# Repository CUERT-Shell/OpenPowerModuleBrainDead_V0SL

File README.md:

# OpenPowerModuleBrainDead_V0SL

Kicad Design 
You can view on https://kicanvas.org (for non kicad users)

## Power Module Board

Minimal BLDC drive hardware
Minimal Fabrication requirements , Single Layer PCB

### The hardware 
* 3phase H-bridge and all its related circuitry (MGD , Snubber , decoupling , etc)

Requires External 12V supply in addition to DC bus voltage

## Power Module Interface Board

* IDC-2x15 Connector to be interfaced with a controller/MCU
* 12V-->5V buck converter , 3.3V LDO
* Hall Sensor Conditioning Circuits
* Back Emf Zero cross detection circuitry
* Phase Voltage Conditioning Circuitry
* 3x NTC interface
* IDC-2x15 Connector to be interfaced with a controller/MCU
* LED as logic indicators

Requires External 12V supply

### Repo Structure
* PowerModule : Power Module Design Files
* PowerModuleInterface : Power Module Interface Design Files
* LIB : Project Components library
* Doc : Design Reference , guide , step file , etc...

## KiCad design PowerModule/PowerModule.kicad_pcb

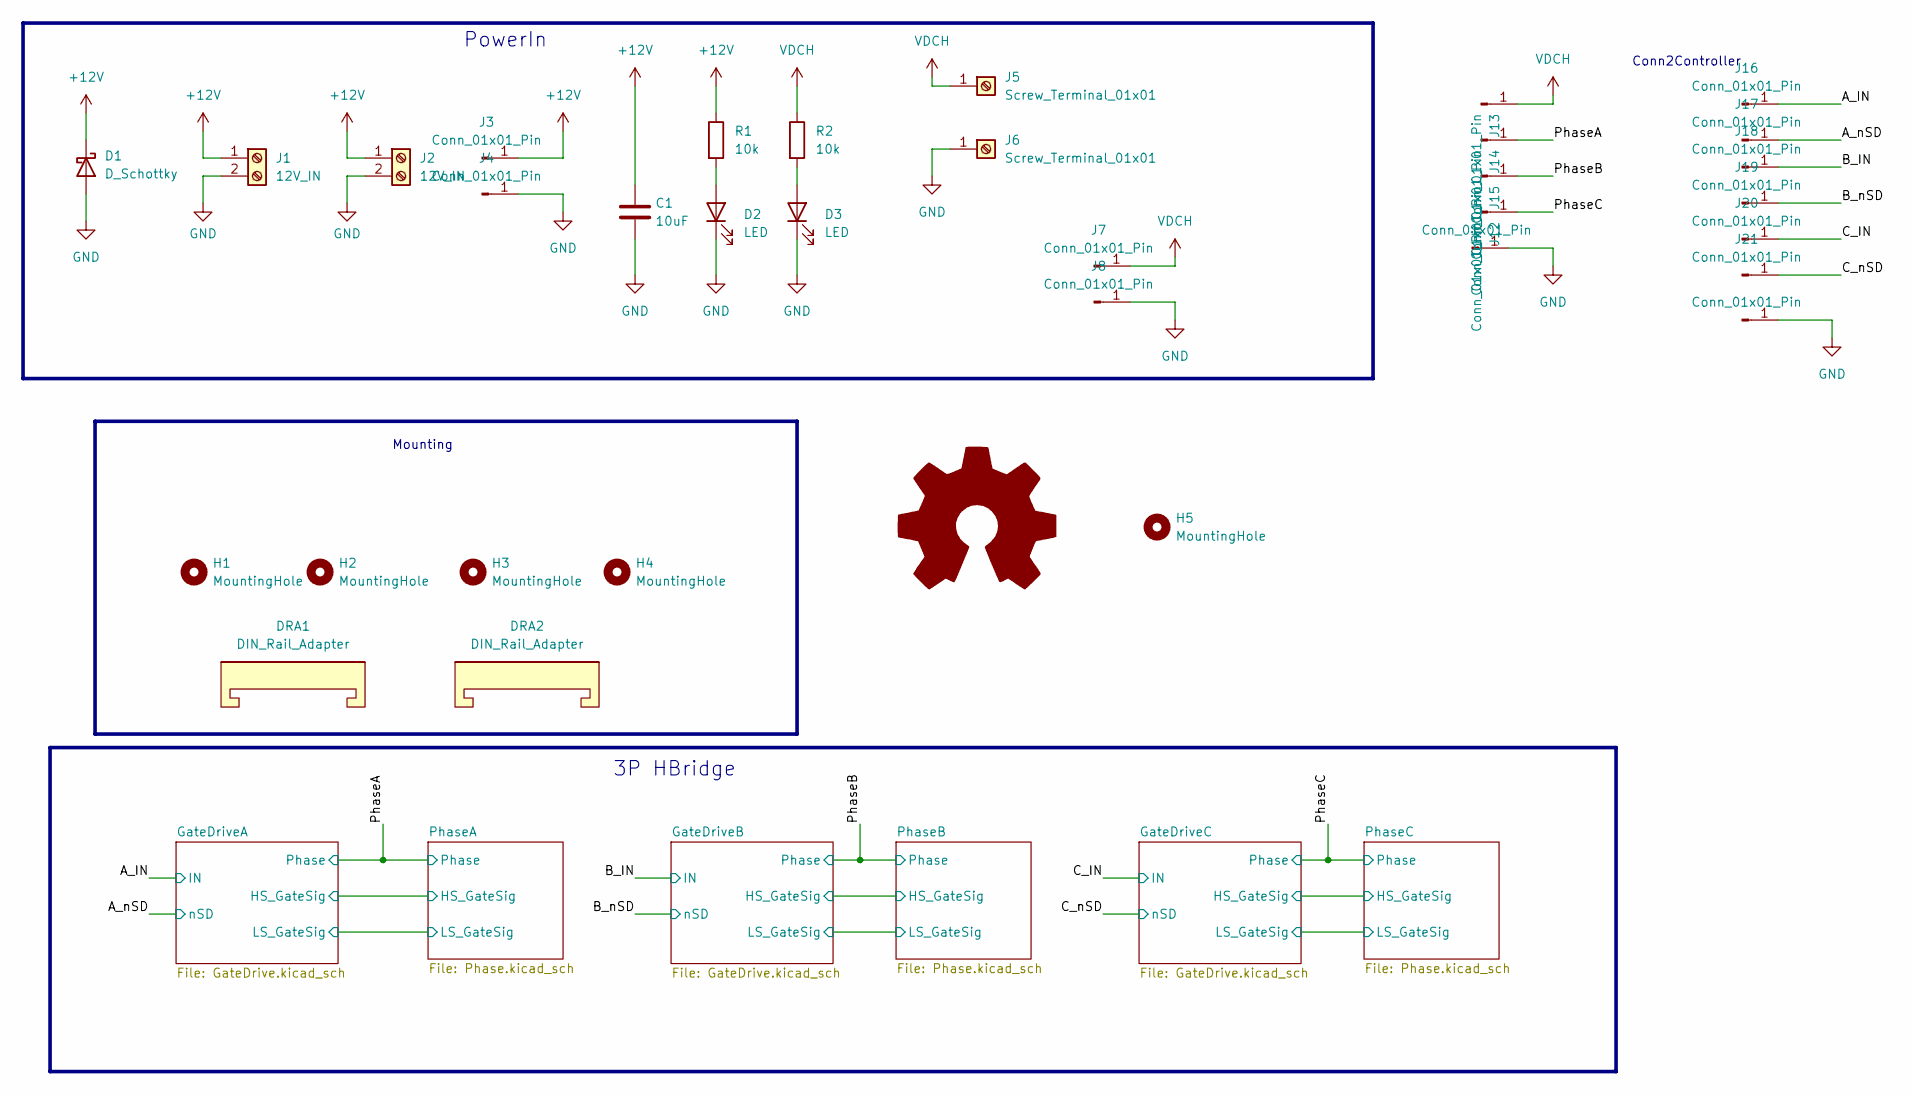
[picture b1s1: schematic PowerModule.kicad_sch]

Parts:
C1: 10uF; C_1206_3216Metric
D1: D_Schottky; D_SMC-RM10_Universal_Handsoldering
D2, D3: LED; LED_1206_3216Metric_Pad1.42x1.75mm_HandSolder
DRA1, DRA2: DIN_Rail_Adapter; DinRailPCBClip_P15
H1, H2, H3, H4: MountingHole; MountingHole_3.2mm_M3_DIN965
H5: MountingHole; KiCad-Logo2_12mm_SilkScreen
J1, J2: 12V_IN; TerminalBlock_Phoenix_PT-1,5-2-3.5-H_1x02_P3.50mm_Horizontal
J3, J4, J7, J8, J11, J12, J13, J14, J15, J16, J17, J18, J19, J20, J21, J22: Conn_01x01_Pin; WirePad_2.5x5
J5, J6: Screw_Terminal_01x01; D5mm_WirePad
R1, R2: 10k; R_1206_3216Metric_Pad1.30x1.75mm_HandSolder

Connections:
+12V: C1.1, D1.1 (K), J1.1, J2.1, J3.1, R1.1; also elsewhere on the board
/A_IN: J16.1; also elsewhere on the board
/A_nSD: J17.1; also elsewhere on the board
/B_IN: J18.1; also elsewhere on the board
/B_nSD: J19.1; also elsewhere on the board
/C_IN: J20.1; also elsewhere on the board
/C_nSD: J21.1; also elsewhere on the board
/PhaseA: J14.1; also elsewhere on the board
/PhaseB: J15.1; also elsewhere on the board
/PhaseC: J12.1; also elsewhere on the board
GND: C1.2, D1.2 (A), D2.1 (K), D3.1 (K), J1.2, J2.2, J4.1, J6.1, J8.1, J11.1, J22.1; also elsewhere on the board
unnamed: D2.2 (A), R1.2
unnamed: D3.2 (A), R2.2
VDCH: J5.1, J7.1, J13.1, R2.1; also elsewhere on the board

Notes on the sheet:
Mounting
3P HBridge
Conn2Controller
PowerIn

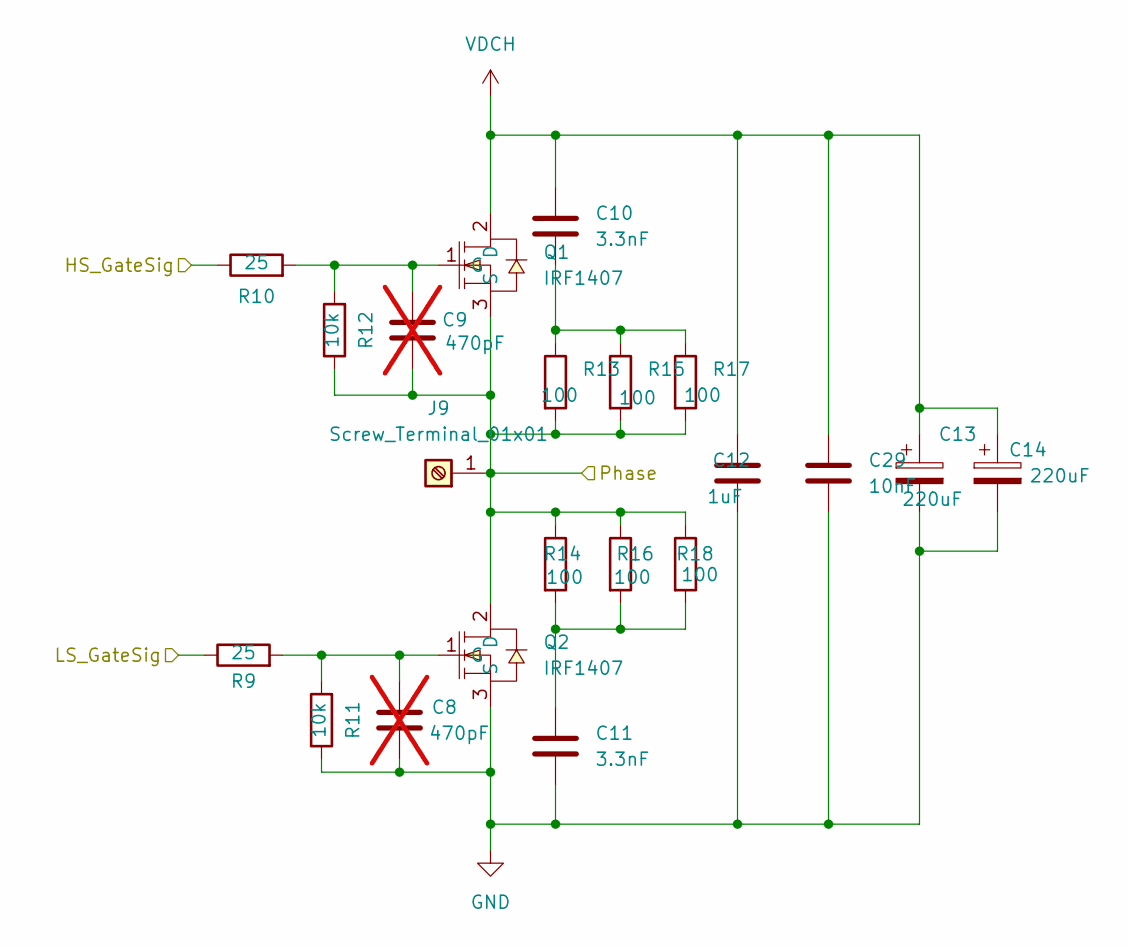
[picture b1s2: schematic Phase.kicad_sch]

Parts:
C8, C9: 470pF; C_1206_3216Metric; not fitted
C10, C11: 3.3nF; C_Rect_L7.2mm_W3.5mm_P5.00mm_FKS2_FKP2_MKS2_MKP2
C12: 1uF; C_Rect_L9.0mm_W5.1mm_P7.50mm_MKT
C13: 220uF; CP_Radial_Horizontal_P5.00_Up
C14: 220uF; CP_Radial_Horizontal_P5.00_Down
C29: 10nF; C_Rect_L7.2mm_W3.5mm_P5.00mm_FKS2_FKP2_MKS2_MKP2
J9: Screw_Terminal_01x01; D5mm_WirePad
Q1, Q2: IRF1407; TO-220-3_Horizontal_TabUp; LCSC Part C33129604
R9, R10: 25; R_1206_3216Metric
R11, R12: 10k; R_1206_3216Metric
R13, R14, R15, R16, R17, R18: 100; R_1206_3216Metric

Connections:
/GateDriveA/HS_GateSig: R10.1; also elsewhere on the board
/GateDriveA/LS_GateSig: R9.1; also elsewhere on the board
/PhaseA: C9.2, J9.1, Q1.3 (S), Q2.2 (D), R12.1, R13.2, R14.1, R15.2, R16.1, R17.2, R18.1; also elsewhere on the board
GND: C8.2, C11.2, C12.2, C13.2, C14.2, C29.2, Q2.3 (S), R11.1; also elsewhere on the board
unnamed: C10.2, R13.1, R15.1, R17.1
unnamed: C11.1, R14.2, R16.2, R18.2
unnamed: C9.1, Q1.1 (G), R10.2, R12.2
unnamed: C8.1, Q2.1 (G), R9.2, R11.2
VDCH: C10.1, C12.1, C13.1, C14.1, C29.1, Q1.2 (D); also elsewhere on the board

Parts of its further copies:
C15, C16, C22, C23: 470pF; C_1206_3216Metric; not fitted
C17, C18, C24, C25: 3.3nF; C_Rect_L7.2mm_W3.5mm_P5.00mm_FKS2_FKP2_MKS2_MKP2
C19, C26: 1uF; C_Rect_L9.0mm_W5.1mm_P7.50mm_MKT
C20, C27: 220uF; CP_Radial_Horizontal_P5.00_Up
C21, C28: 220uF; CP_Radial_Horizontal_P5.00_Down
C30, C31: 10nF; C_Rect_L7.2mm_W3.5mm_P5.00mm_FKS2_FKP2_MKS2_MKP2
J10, J23: Screw_Terminal_01x01; D5mm_WirePad
Q3, Q4, Q5, Q6: IRF1407; TO-220-3_Horizontal_TabUp; LCSC Part C33129604
R19, R20, R29, R30: 25; R_1206_3216Metric
R21, R22, R31, R32: 10k; R_1206_3216Metric
R23, R24, R25, R26, R27, R28, R33, R34, R35, R36, R37, R38: 100; R_1206_3216Metric

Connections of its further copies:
/GateDriveB/HS_GateSig: R20.1; also elsewhere on the board
/GateDriveB/LS_GateSig: R19.1; also elsewhere on the board
/GateDriveC/HS_GateSig: R30.1; also elsewhere on the board
/GateDriveC/LS_GateSig: R29.1; also elsewhere on the board
/PhaseB: C16.2, J10.1, Q3.3 (S), Q4.2 (D), R22.1, R23.2, R24.1, R25.2, R26.1, R27.2, R28.1; also elsewhere on the board
/PhaseC: C23.2, J23.1, Q5.3 (S), Q6.2 (D), R32.1, R33.2, R34.1, R35.2, R36.1, R37.2, R38.1; also elsewhere on the board
GND: C15.2, C18.2, C19.2, C20.2, C21.2, C22.2, C25.2, C26.2, C27.2, C28.2, C30.2, C31.2, Q4.3 (S), Q6.3 (S), R21.1, R31.1; also elsewhere on the board
unnamed: C17.2, R23.1, R25.1, R27.1
unnamed: C18.1, R24.2, R26.2, R28.2
unnamed: C24.2, R33.1, R35.1, R37.1
unnamed: C25.1, R34.2, R36.2, R38.2
unnamed: C16.1, Q3.1 (G), R20.2, R22.2
unnamed: C15.1, Q4.1 (G), R19.2, R21.2
unnamed: C23.1, Q5.1 (G), R30.2, R32.2
unnamed: C22.1, Q6.1 (G), R29.2, R31.2
VDCH: C17.1, C19.1, C20.1, C21.1, C24.1, C26.1, C27.1, C28.1, C30.1, C31.1, Q3.2 (D), Q5.2 (D); also elsewhere on the board

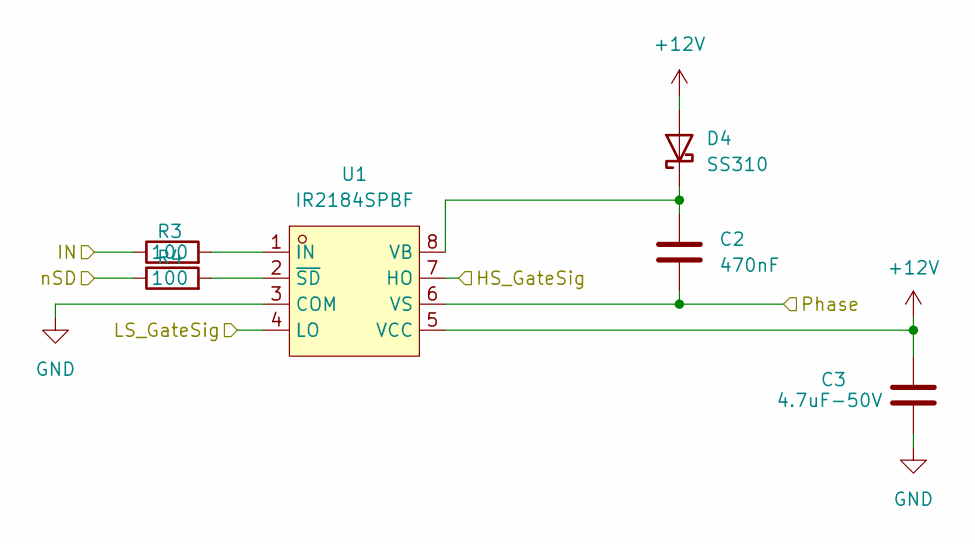
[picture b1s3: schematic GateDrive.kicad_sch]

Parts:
C2: 470nF; C_Rect_L9.0mm_W5.1mm_P7.50mm_MKT
C3: 4.7uF-50V; C_1206_3216Metric
D4: SS310; D_SMC-RM10_Universal_Handsoldering
R3, R4: 100; R_1206_3216Metric
U1: IR2184SPBF; SOIC-8_L5.0-W4.0-P1.27-LS6.0-BL; LCSC Part C537610

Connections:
+12V: C3.1, D4.2 (A), U1.5 (VCC); also elsewhere on the board
/A_IN: R3.1; also elsewhere on the board
/A_nSD: R4.1; also elsewhere on the board
/GateDriveA/HS_GateSig: U1.7 (HO); also elsewhere on the board
/GateDriveA/LS_GateSig: U1.4 (LO); also elsewhere on the board
/PhaseA: C2.2, U1.6 (VS); also elsewhere on the board
GND: C3.2, U1.3 (COM); also elsewhere on the board
unnamed: C2.1, D4.1 (K), U1.8 (VB)
unnamed: R3.2, U1.1 (IN)
unnamed: R4.2, U1.2 (~SD)

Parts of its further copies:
C4, C6: 470nF; C_Rect_L9.0mm_W5.1mm_P7.50mm_MKT
C5, C7: 4.7uF-50V; C_1206_3216Metric
D5, D6: SS310; D_SMC-RM10_Universal_Handsoldering
R5, R6, R7, R8: 100; R_1206_3216Metric
U2, U3: IR2184SPBF; SOIC-8_L5.0-W4.0-P1.27-LS6.0-BL; LCSC Part C537610

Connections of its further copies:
+12V: C5.1, C7.1, D5.2 (A), D6.2 (A), U2.5 (VCC), U3.5 (VCC); also elsewhere on the board
/B_IN: R5.1; also elsewhere on the board
/B_nSD: R6.1; also elsewhere on the board
/C_IN: R7.1; also elsewhere on the board
/C_nSD: R8.1; also elsewhere on the board
/GateDriveB/HS_GateSig: U2.7 (HO); also elsewhere on the board
/GateDriveB/LS_GateSig: U2.4 (LO); also elsewhere on the board
/GateDriveC/HS_GateSig: U3.7 (HO); also elsewhere on the board
/GateDriveC/LS_GateSig: U3.4 (LO); also elsewhere on the board
/PhaseB: C4.2, U2.6 (VS); also elsewhere on the board
/PhaseC: C6.2, U3.6 (VS); also elsewhere on the board
GND: C5.2, C7.2, U2.3 (COM), U3.3 (COM); also elsewhere on the board
unnamed: C4.1, D5.1 (K), U2.8 (VB)
unnamed: C6.1, D6.1 (K), U3.8 (VB)
unnamed: R5.2, U2.1 (IN)
unnamed: R6.2, U2.2 (~SD)
unnamed: R7.2, U3.1 (IN)
unnamed: R8.2, U3.2 (~SD)

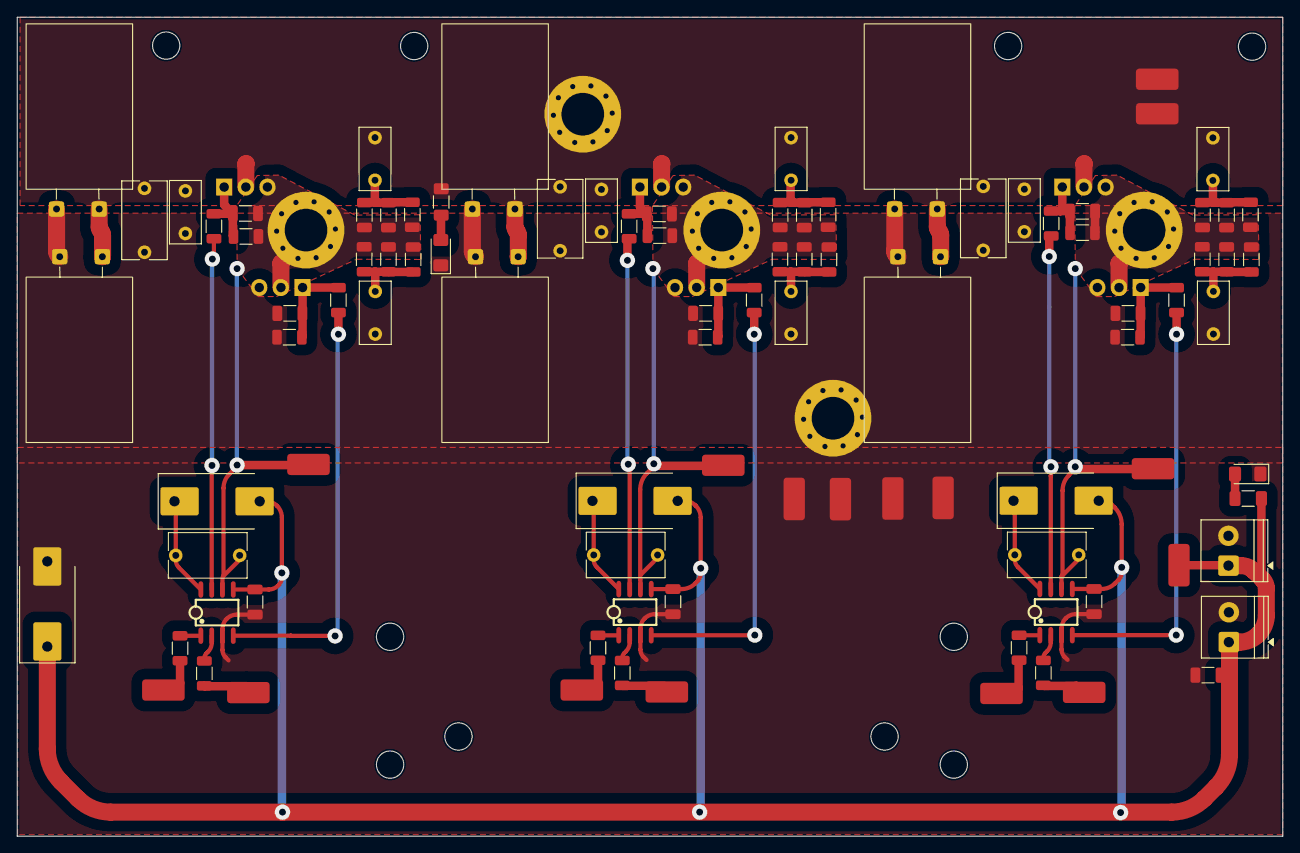
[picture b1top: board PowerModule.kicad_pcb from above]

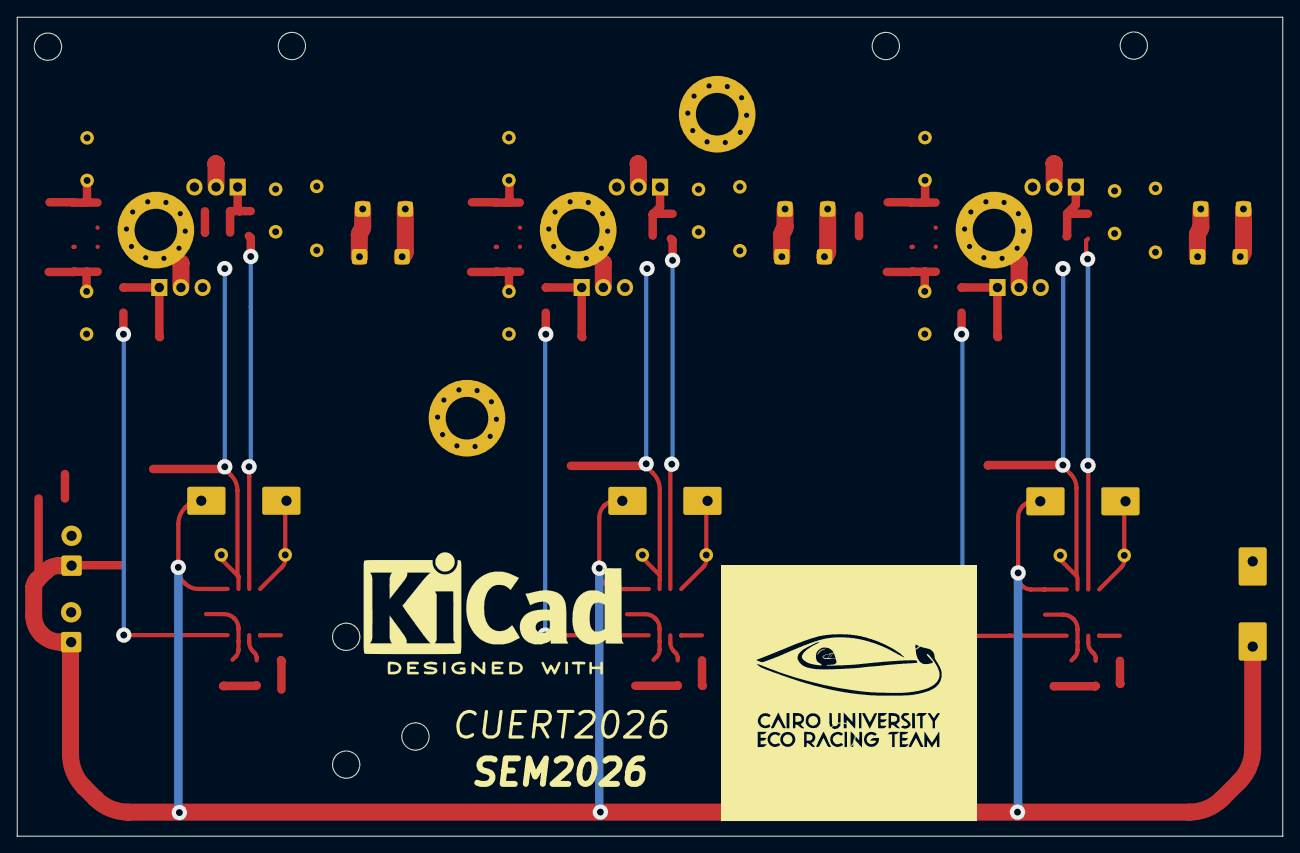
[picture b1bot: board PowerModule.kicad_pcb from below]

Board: 2 copper layers, 148.5 x 96.1 mm, 114 parts (7 on the bottom side), 41 nets.

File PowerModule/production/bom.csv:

Designator,Footprint,Quantity,Value,LCSC Part #
C1,1206,1,10uF,
"C10, C11, C17, C18, C24, C25",C_Rect_L7.2mm_W3.5mm_P5.00mm_FKS2_FKP2_MKS2_MKP2,6,3.3nF,
"C12, C19, C26",C_Rect_L9.0mm_W5.1mm_P7.50mm_MKT,3,1uF,
"C13, C20, C27",CP_Radial_Horizontal_P5.00_Up,3,220uF,
"C14, C21, C28",CP_Radial_Horizontal_P5.00_Down,3,220uF,
"C15, C16, C22, C23, C8, C9",1206,6,470pF,
"C2, C4, C6",C_Rect_L9.0mm_W5.1mm_P7.50mm_MKT,3,470nF,
"C29, C30, C31",C_Rect_L7.2mm_W3.5mm_P5.00mm_FKS2_FKP2_MKS2_MKP2,3,10nF,
"C3, C5, C7",1206,3,4.7uF-50V,
D1,D_SMC-RM10_Universal_Handsoldering,1,D_Schottky,
"D2, D3",1206,2,LED,
"D4, D5, D6",D_SMC-RM10_Universal_Handsoldering,3,SS310,
"DRA1, DRA2",DinRailPCBClip_P15,2,DIN_Rail_Adapter,
"J1, J2","TerminalBlock_Phoenix_PT-1,5-2-3.5-H_1x02_P3.50mm_Horizontal",2,12V_IN,
"J10, J23, J5, J6, J9",D5mm_WirePad,5,Screw_Terminal_01x01,
"J11, J12, J13, J14, J15, J16, J17, J18, J19, J20, J21, J22, J3, J4, J7, J8",WirePad_2.5x5,16,Conn_01x01_Pin,
"Q1, Q2, Q3, Q4, Q5, Q6",TO-220-3_Horizontal_TabUp,6,IRF1407,C33129604
"R1, R11, R12, R2, R21, R22, R31, R32",1206,8,10k,
"R10, R19, R20, R29, R30, R9",1206,6,25,
"R13, R14, R15, R16, R17, R18, R23, R24, R25, R26, R27, R28, R3, R33, R34, R35, R36, R37, R38, R4, R5, R6, R7, R8",1206,24,100,
"U1, U2, U3",SOIC-8_L5.0-W4.0-P1.27-LS6.0-BL,3,IR2184SPBF,C537610

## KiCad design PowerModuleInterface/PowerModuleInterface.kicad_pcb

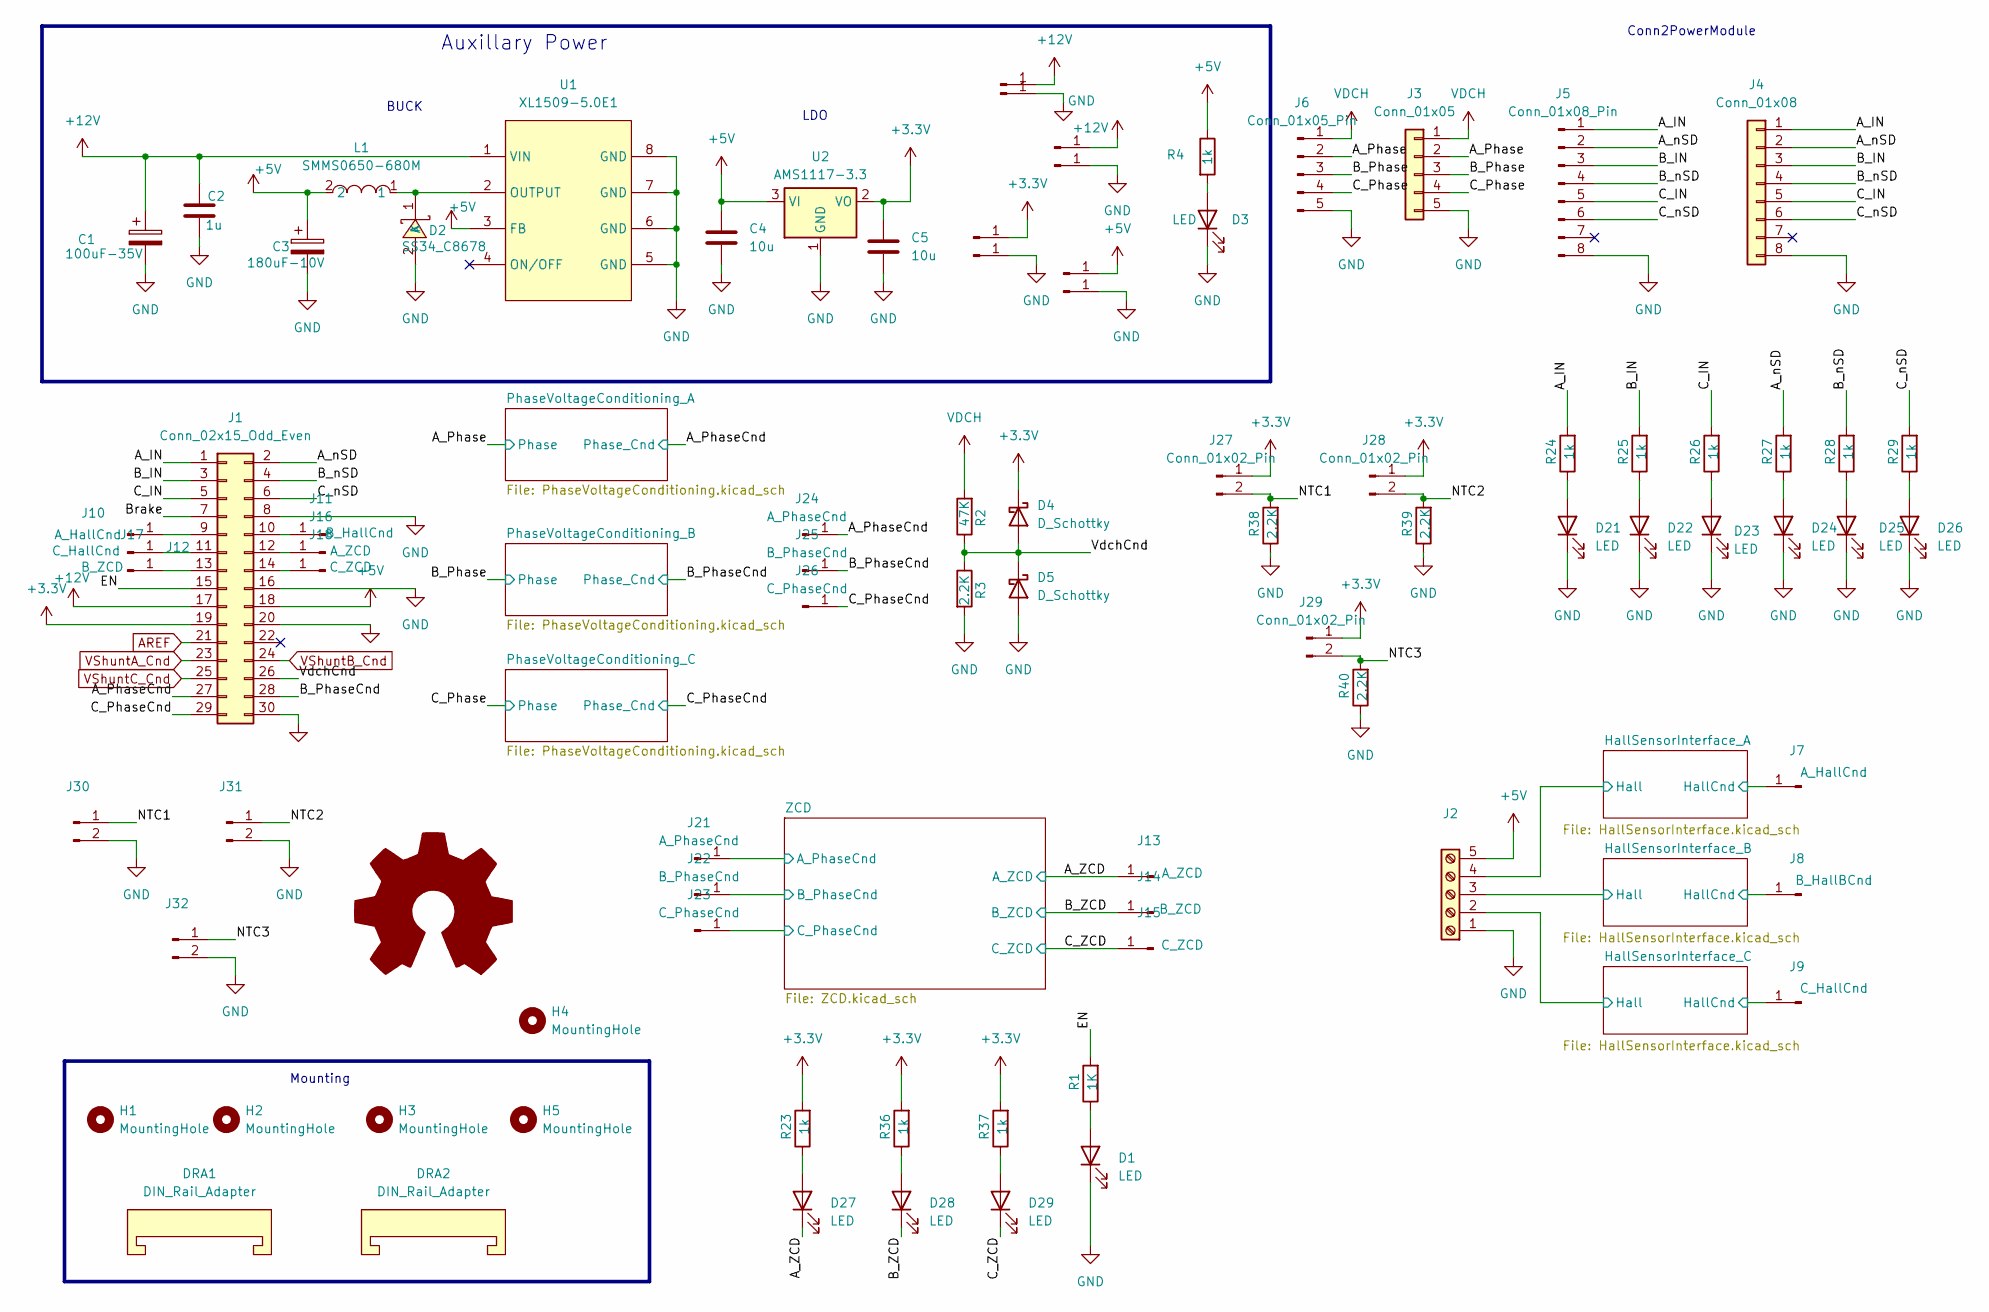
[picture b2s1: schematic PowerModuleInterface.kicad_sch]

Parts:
C1: 100uF-35V; CP_Radial_D6.3mm_P2.50mm
C2: 1u; C_1206_3216Metric
C3: 180uF-10V; CP_Radial_D6.3mm_P2.50mm
C4, C5: 10u; C_1206_3216Metric
D1, D3, D21, D22, D23, D24, D25, D26, D27, D28, D29: LED; LED_D3.0mm
D2: SS34_C8678; SMA_L4.3-W2.6-LS5.2-RD; LCSC Part C8678
D4, D5: D_Schottky; D_SOD-123; LCSC Part C181204
DRA1, DRA2: DIN_Rail_Adapter; DinRailPCBClip_P15
H1, H2, H3, H5: MountingHole; MountingHole_3.2mm_M3_DIN965
H4: MountingHole; KiCad-Logo2_6mm_SilkScreen
J1: Conn_02x15_Odd_Even; IDC-Header_2x15_P2.54mm_Vertical
J2: Screw_Terminal_01x05; TerminalBlock_Phoenix_PT-1,5-5-3.5-H_1x05_P3.50mm_Horizontal
J3: Conn_01x05; JST_XH_B5B-XH-A_1x05_P2.50mm_Vertical
J4: Conn_01x08; JST_XH_B8B-XH-A_1x08_P2.50mm_Vertical
J5: Conn_01x08_Pin; PinHeader_1x08_P2.54mm_Vertical
J6: Conn_01x05_Pin; PinHeader_1x05_P2.54mm_Vertical
J7, J10: A_HallCnd; WirePad_2.5x5
J8: B_HallBCnd; WirePad_2.5x5
J9, J12: C_HallCnd; WirePad_2.5x5
J11: B_HallCnd; WirePad_2.5x5
J13, J16: A_ZCD; WirePad_2.5x5
J14, J17: B_ZCD; WirePad_2.5x5
J15, J18: C_ZCD; WirePad_2.5x5
J19, J20, J33, J34, J35, J36, J37, J38: Conn_01x01_Pin; WirePad_2.5x5
J21, J24: A_PhaseCnd; WirePad_2.5x5
J22, J25: B_PhaseCnd; WirePad_2.5x5
J23, J26: C_PhaseCnd; WirePad_2.5x5
J27, J28, J29, J30, J31, J32: Conn_01x02_Pin; PinHeader_1x02_P2.54mm_Vertical
L1: SMMS0650-680M; IND-SMD_L7.1-W6.6_H5.0; LCSC Part C2894721
R1: 1K; R_1206_3216Metric; LCSC Part C113307
R2: 47K; R_1206_3216Metric
R3: 2.2K; R_1206_3216Metric
R4: 1k; R_1206_3216Metric
R23, R24, R25, R26, R27, R28, R29, R36, R37: 1k; R_1206_3216Metric; LCSC Part C113307
R38, R39, R40: 2.2K; R_1206_3216Metric; LCSC Part C113307
U1: XL1509-5.0E1; SOIC-8_L5.0-W4.0-P1.27-LS6.0-BL; LCSC Part C61063
U2: AMS1117-3.3; SOT-223-3_TabPin2

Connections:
+3.3V: C5.1, D4.1 (K), J1.19, J27.1, J28.1, J29.1, J37.1, R23.2, R36.2, R37.2, U2.2 (VO); also elsewhere on the board
+5V: C3.1, C4.1, J1.18, J2.5, J33.1, L1.2, R4.1, U1.3 (FB), U2.3 (VI)
+12V: C1.1, C2.1, J1.17, J19.1, J35.1, U1.1 (VIN); also elsewhere on the board
/A_IN: J1.1, J4.1, J5.1, R24.2
/A_Phase: J3.2, J6.2; also elsewhere on the board
/A_PhaseCnd: J1.27, J24.1; also elsewhere on the board
/A_ZCD: D27.1 (K), J13.1; also elsewhere on the board
/A_nSD: J1.2, J4.2, J5.2, R27.2
/B_IN: J1.3, J4.3, J5.3, R25.2
/B_Phase: J3.3, J6.3; also elsewhere on the board
/B_PhaseCnd: J1.28, J25.1; also elsewhere on the board
/B_ZCD: D28.1 (K), J14.1; also elsewhere on the board
/B_nSD: J1.4, J4.4, J5.4, R28.2
/Brake: J1.7
/C_IN: J1.5, J4.5, J5.5, R26.2
/C_Phase: J3.4, J6.4; also elsewhere on the board
/C_PhaseCnd: J1.29, J26.1; also elsewhere on the board
/C_ZCD: D29.1 (K), J15.1; also elsewhere on the board
/C_nSD: J1.6, J4.6, J5.6, R29.2
/EN: J1.15, R1.2
/HallSensorInterface_A/Hall: J2.4; also elsewhere on the board
/HallSensorInterface_A/HallCnd: J7.1; also elsewhere on the board
/HallSensorInterface_B/Hall: J2.3; also elsewhere on the board
/HallSensorInterface_B/HallCnd: J8.1; also elsewhere on the board
/HallSensorInterface_C/Hall: J2.2; also elsewhere on the board
/HallSensorInterface_C/HallCnd: J9.1; also elsewhere on the board
/NTC1: J27.2, J30.1, R38.2
/NTC2: J28.2, J31.1, R39.2
/NTC3: J29.2, J32.1, R40.2
/VdchCnd: D4.2 (A), D5.1 (K), J1.26, R2.1, R3.1
/ZCD/A_PhaseCnd: J21.1; also elsewhere on the board
/ZCD/B_PhaseCnd: J22.1; also elsewhere on the board
/ZCD/C_PhaseCnd: J23.1; also elsewhere on the board
AREF: J1.21
GND: C1.2, C2.2, C3.2, C4.2, C5.2, D1.1 (K), D2.2 (A), D3.1 (K), D5.2 (A), D21.1 (K), D22.1 (K), D23.1 (K), D24.1 (K), D25.1 (K), D26.1 (K), J1.8, J1.16, J1.20, J1.30, J2.1, J3.5, J4.8, J5.8, J6.5, J20.1, J30.2, J31.2, J32.2, J34.1, J36.1, J38.1, R3.2, R38.1, R39.1, R40.1, U1.5 (GND), U1.6 (GND), U1.7 (GND), U1.8 (GND), U2.1 (GND); also elsewhere on the board
unnamed: D1.2 (A), R1.1
unnamed: D2.1 (K), L1.1, U1.2 (OUTPUT)
unnamed: D3.2 (A), R4.2
unnamed: D21.2 (A), R24.1
unnamed: D22.2 (A), R25.1
unnamed: D23.2 (A), R26.1
unnamed: D24.2 (A), R27.1
unnamed: D25.2 (A), R28.1
unnamed: D26.2 (A), R29.1
unnamed: D27.2 (A), R23.1
unnamed: D28.2 (A), R36.1
unnamed: D29.2 (A), R37.1
unnamed: J1.9, J10.1
unnamed: J1.10, J11.1
unnamed: J1.11, J12.1
unnamed: J1.12, J16.1
unnamed: J1.13, J17.1
unnamed: J1.14, J18.1
VDCH: J3.1, J6.1, R2.2
VShuntA_Cnd: J1.23
VShuntB_Cnd: J1.24
VShuntC_Cnd: J1.25

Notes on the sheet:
Conn2PowerModule
Mounting
BUCK
LDO
Auxillary Power

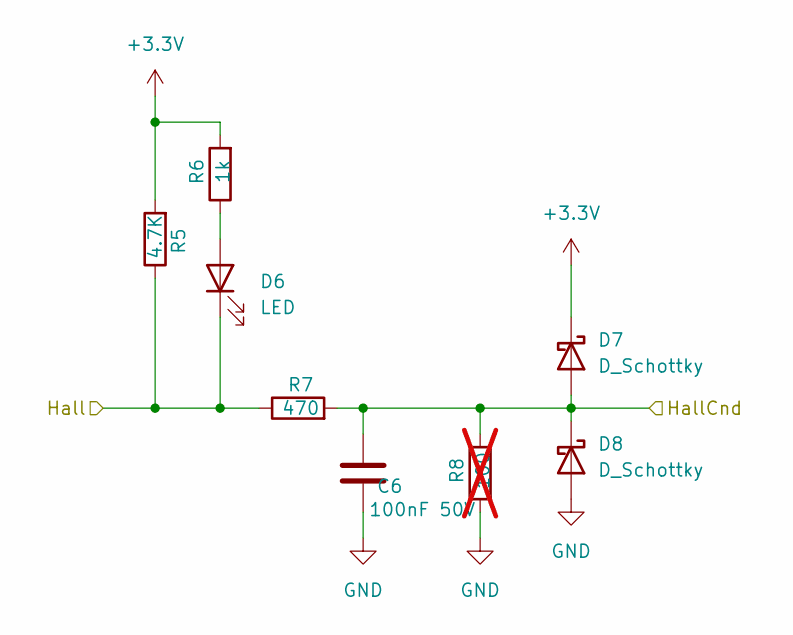
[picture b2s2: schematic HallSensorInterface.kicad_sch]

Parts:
C6: 100nF 50V; C_1206_3216Metric; LCSC Part C24497
D6: LED; LED_D3.0mm
D7, D8: D_Schottky; D_SOD-123; LCSC Part C181204
R5: 4.7K; R_1206_3216Metric; LCSC Part C17902
R6: 1k; R_1206_3216Metric; LCSC Part C113307
R7: 470; R_1206_3216Metric; LCSC Part C113307
R8: 100; R_1206_3216Metric; LCSC Part C113307; not fitted

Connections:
+3.3V: D7.1 (K), R5.2, R6.2; also elsewhere on the board
/HallSensorInterface_B/Hall: D6.1 (K), R5.1, R7.1; also elsewhere on the board
/HallSensorInterface_B/HallCnd: C6.1, D7.2 (A), D8.1 (K), R7.2, R8.2; also elsewhere on the board
GND: C6.2, D8.2 (A), R8.1; also elsewhere on the board
unnamed: D6.2 (A), R6.1

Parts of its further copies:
C8, C9: 100nF 50V; C_1206_3216Metric; LCSC Part C24497
D11, D14: LED; LED_D3.0mm
D12, D13, D15, D16: D_Schottky; D_SOD-123; LCSC Part C181204
R11, R15: 4.7K; R_1206_3216Metric; LCSC Part C17902
R12, R16: 1k; R_1206_3216Metric; LCSC Part C113307
R13, R17: 470; R_1206_3216Metric; LCSC Part C113307
R14, R18: 100; R_1206_3216Metric; LCSC Part C113307; not fitted

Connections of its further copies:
+3.3V: D12.1 (K), D15.1 (K), R11.2, R12.2, R15.2, R16.2; also elsewhere on the board
/HallSensorInterface_A/Hall: D14.1 (K), R15.1, R17.1; also elsewhere on the board
/HallSensorInterface_A/HallCnd: C9.1, D15.2 (A), D16.1 (K), R17.2, R18.2; also elsewhere on the board
/HallSensorInterface_C/Hall: D11.1 (K), R11.1, R13.1; also elsewhere on the board
/HallSensorInterface_C/HallCnd: C8.1, D12.2 (A), D13.1 (K), R13.2, R14.2; also elsewhere on the board
GND: C8.2, C9.2, D13.2 (A), D16.2 (A), R14.1, R18.1; also elsewhere on the board
unnamed: D11.2 (A), R12.1
unnamed: D14.2 (A), R16.1

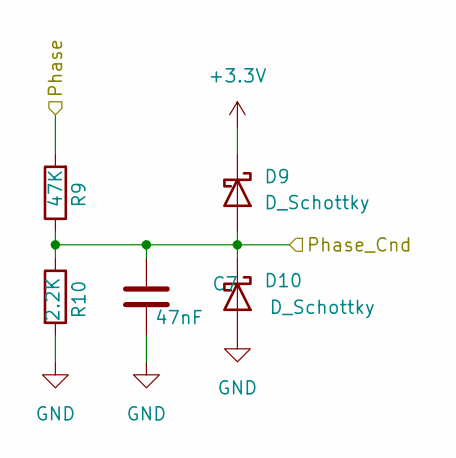
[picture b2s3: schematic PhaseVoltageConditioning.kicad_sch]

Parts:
C7: 47nF; C_1206_3216Metric
D9, D10: D_Schottky; D_SOD-123; LCSC Part C181204
R9: 47K; R_1206_3216Metric
R10: 2.2K; R_1206_3216Metric

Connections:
+3.3V: D9.1 (K); also elsewhere on the board
/A_Phase: R9.2; also elsewhere on the board
/A_PhaseCnd: C7.1, D9.2 (A), D10.1 (K), R9.1, R10.1; also elsewhere on the board
GND: C7.2, D10.2 (A), R10.2; also elsewhere on the board

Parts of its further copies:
C10, C11: 47nF; C_1206_3216Metric
D17, D18, D19, D20: D_Schottky; D_SOD-123; LCSC Part C181204
R19, R21: 47K; R_1206_3216Metric
R20, R22: 2.2K; R_1206_3216Metric

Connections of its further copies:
+3.3V: D17.1 (K), D19.1 (K); also elsewhere on the board
/B_Phase: R21.2; also elsewhere on the board
/B_PhaseCnd: C11.1, D19.2 (A), D20.1 (K), R21.1, R22.1; also elsewhere on the board
/C_Phase: R19.2; also elsewhere on the board
/C_PhaseCnd: C10.1, D17.2 (A), D18.1 (K), R19.1, R20.1; also elsewhere on the board
GND: C10.2, C11.2, D18.2 (A), D20.2 (A), R20.2, R22.2; also elsewhere on the board

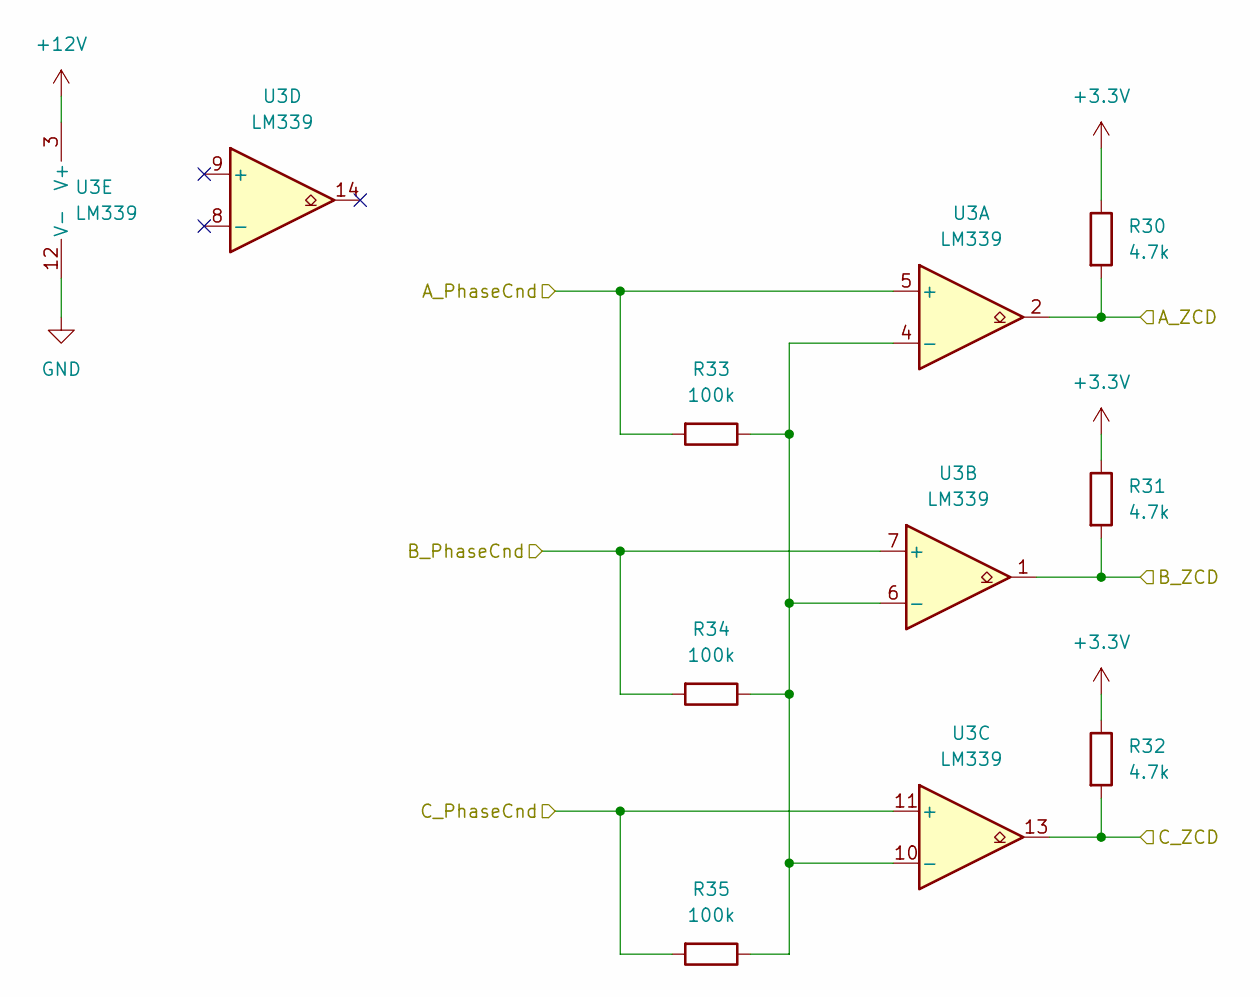
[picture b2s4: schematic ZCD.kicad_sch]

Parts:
R30, R31, R32: 4.7k; R_1206_3216Metric
R33, R34, R35: 100k; R_1206_3216Metric
U3: LM339; SOIC-14_3.9x8.7mm_P1.27mm

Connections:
+3.3V: R30.1, R31.1, R32.1; also elsewhere on the board
+12V: U3.3 (V+); also elsewhere on the board
/A_ZCD: R30.2, U3.2; also elsewhere on the board
/B_ZCD: R31.2, U3.1; also elsewhere on the board
/C_ZCD: R32.2, U3.13; also elsewhere on the board
/ZCD/A_PhaseCnd: R33.2, U3.5 (+); also elsewhere on the board
/ZCD/B_PhaseCnd: R34.2, U3.7 (+); also elsewhere on the board
/ZCD/C_PhaseCnd: R35.2, U3.11 (+); also elsewhere on the board
GND: U3.12 (V-); also elsewhere on the board
unnamed: R33.1, R34.1, R35.1, U3.4 (-), U3.6 (-), U3.10 (-)
